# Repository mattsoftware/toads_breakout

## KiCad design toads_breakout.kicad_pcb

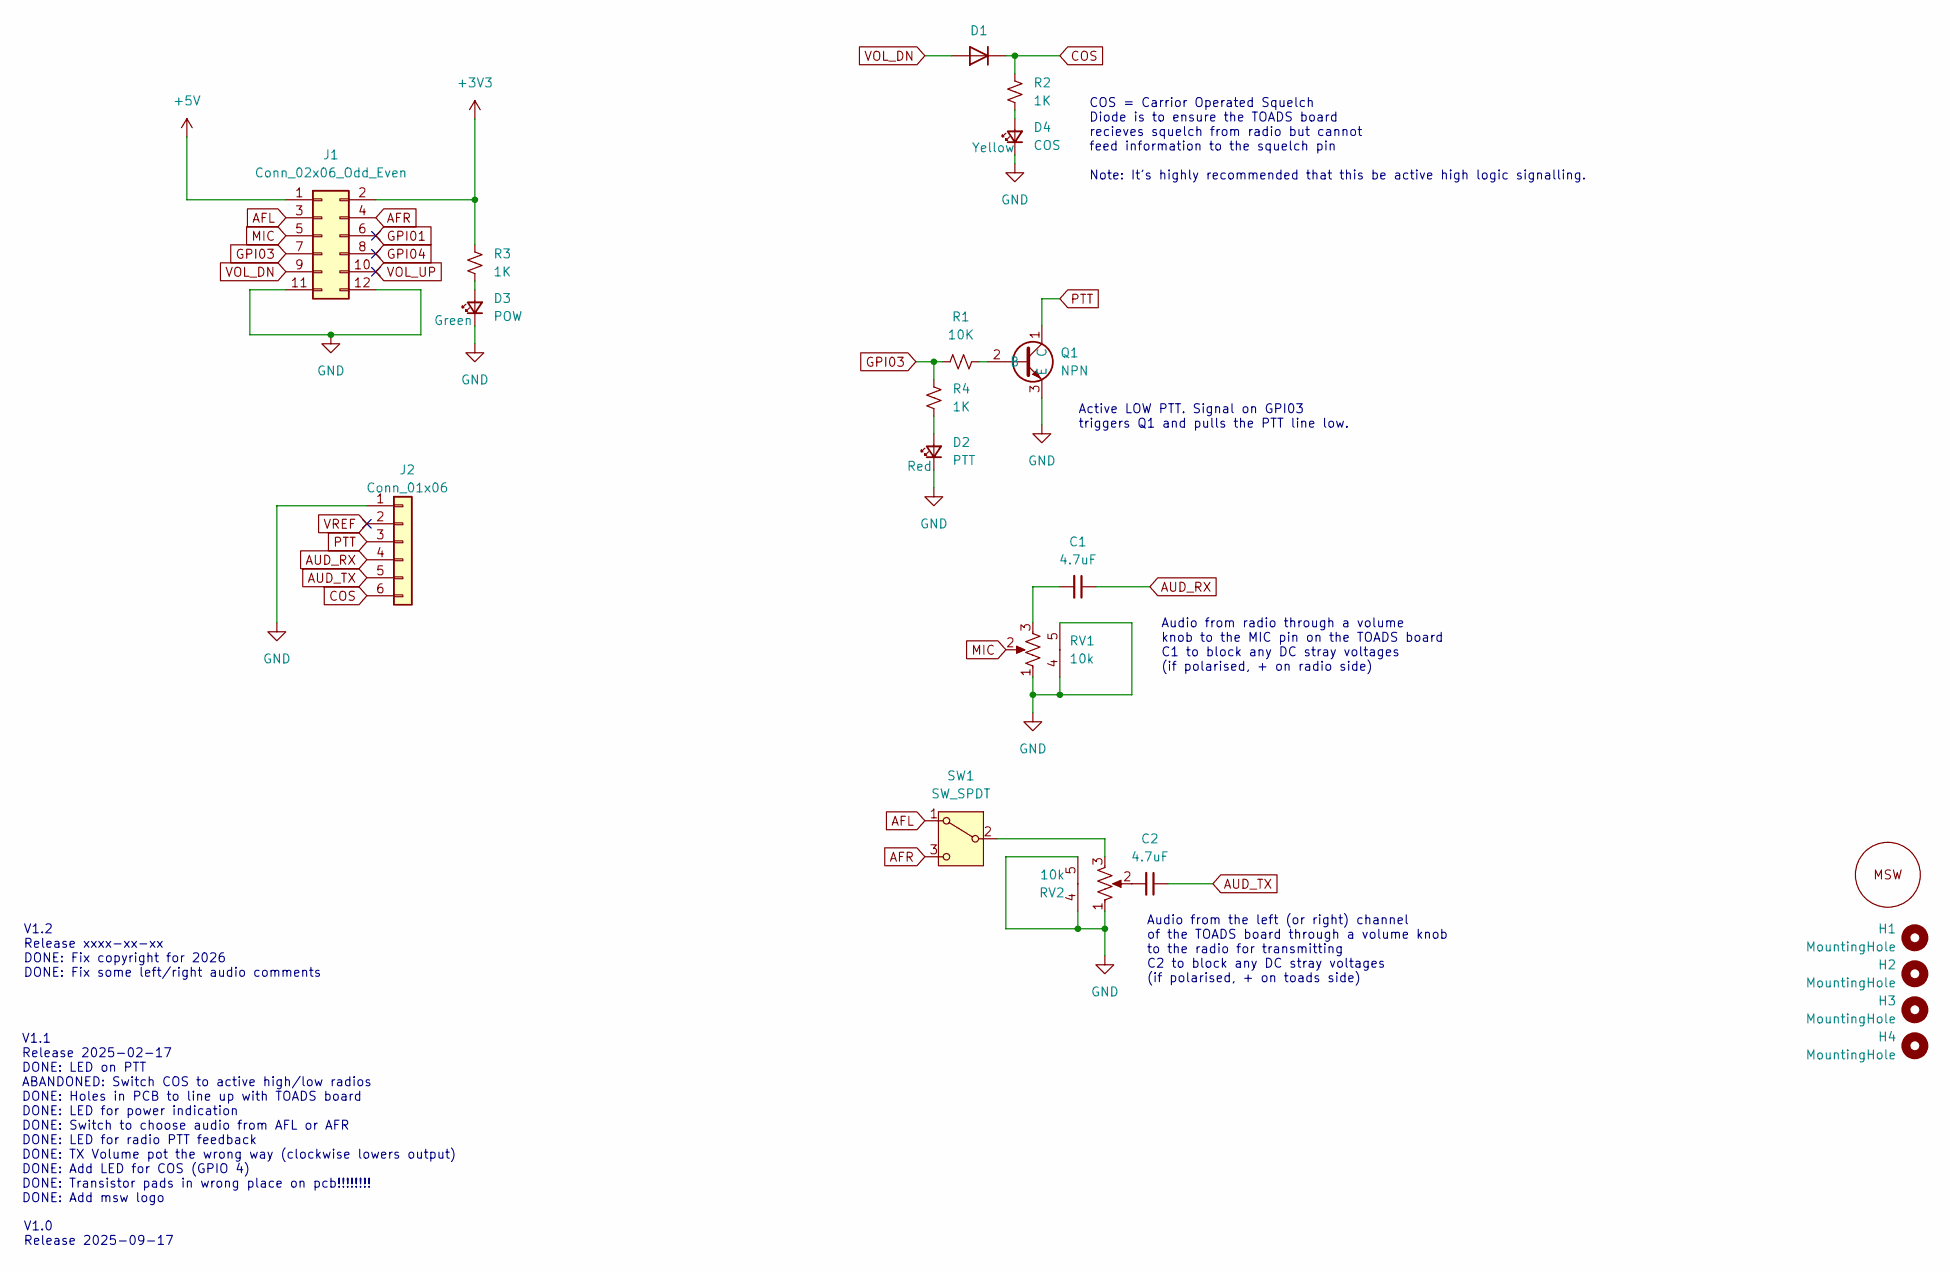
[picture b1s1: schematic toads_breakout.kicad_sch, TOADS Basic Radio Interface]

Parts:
C1, C2: 4.7uF; C_0805_2012Metric_Pad1.18x1.45mm_HandSolder; LCSC# C1779
D1: D_SOD-123FL; LCSC# C64898
D2: PTT; LED_0805_2012Metric; LCSC# C84256
D3: POW; LED_0805_2012Metric; LCSC# C2297
D4: COS; LED_0805_2012Metric; LCSC# C2296
H1, H2, H3, H4: MountingHole; MountingHole_2.5mm_Pad
J1: Conn_02x06_Odd_Even; PinHeader_2x06_P2.54mm_Vertical; LCSC# C124388
J2: Conn_01x06; PinHeader_1x06_P2.54mm_Vertical; LCSC# C37208
Q1: NPN; SOT-23_Handsoldering; LCSC# C2145
R1: 10K; R_0805_2012Metric_Pad1.20x1.40mm_HandSolder; LCSC# C17414
R2, R3, R4: 1K; R_0805_2012Metric_Pad1.20x1.40mm_HandSolder; LCSC# C17513
RV1, RV2: 10k; R_Potentiometer-10k-C361173; LCSC# C361173
SW1: SW_SPDT; SW-SPDT-C49023767; LCSC# C49023767
U1: MSW_Logo; MSW

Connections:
+3V3: J1.2, R3.1
+5V: J1.1
AFL: J1.3, SW1.1 (A)
AFR: J1.4, SW1.3 (C)
AUD_RX: C1.1, J2.4
AUD_TX: C2.1, J2.5
COS: D1.1 (K), J2.6, R2.1
GND: D2.1 (K), D3.1 (K), D4.1 (K), J1.11, J1.12, J2.1, Q1.3 (E), RV1.1, RV1.4, RV1.5, RV2.1, RV2.4, RV2.5
GPI01: J1.6
GPI03: J1.7, R1.1, R4.1
GPI04: J1.8
MIC: J1.5, RV1.2
unnamed: C1.2, RV1.3
unnamed: C2.2, RV2.2
unnamed: D2.2 (A), R4.2
unnamed: D3.2 (A), R3.2
unnamed: D4.2 (A), R2.2
unnamed: Q1.2 (B), R1.2
unnamed: RV2.3, SW1.2 (B)
PTT: J2.3, Q1.1 (C)
VOL_DN: D1.2 (A), J1.9
VOL_UP: J1.10
VREF: J2.2

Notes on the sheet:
Audio from radio through a volume knob to the MIC pin on the TOADS board C1 to block any DC stray voltages (if polarised, + on radio side)
Audio from the left (or right) channel of the TOADS board through a volume knob to the radio for transmitting C2 to block any DC stray voltages (if polarised, + on toads side)
COS = Carrior Operated Squelch Diode is to ensure the TOADS board recieves squelch from radio but cannot feed information to the squelch pin Note: It's highly recommended that this be active high logic signalling.
V1.1 Release 2025-02-17 DONE: LED on PTT ABANDONED: Switch COS to active high/low radios DONE: Holes in PCB to line up with TOADS board DONE: LED for power indication DONE: Switch to choose audio from AFL or AFR DONE: LED for radio PTT feedback DONE: TX Volume pot the wrong way (clockwise lowers ou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
V1.0 Release 2025-09-17
V1.2 Release xxxx-xx-xx DONE: Fix copyright for 2026 DONE: Fix some left/right audio comments
Active LOW PTT. Signal on GPI03 triggers Q1 and pulls the PTT line low.

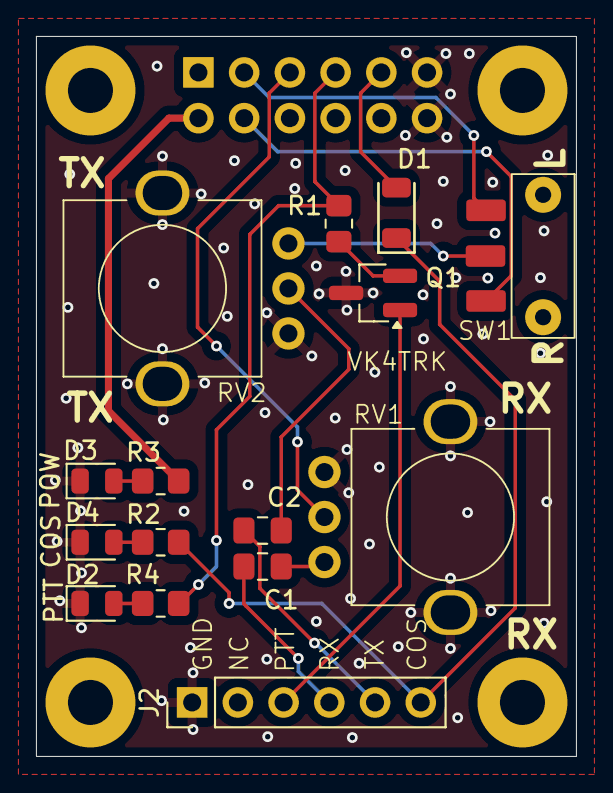
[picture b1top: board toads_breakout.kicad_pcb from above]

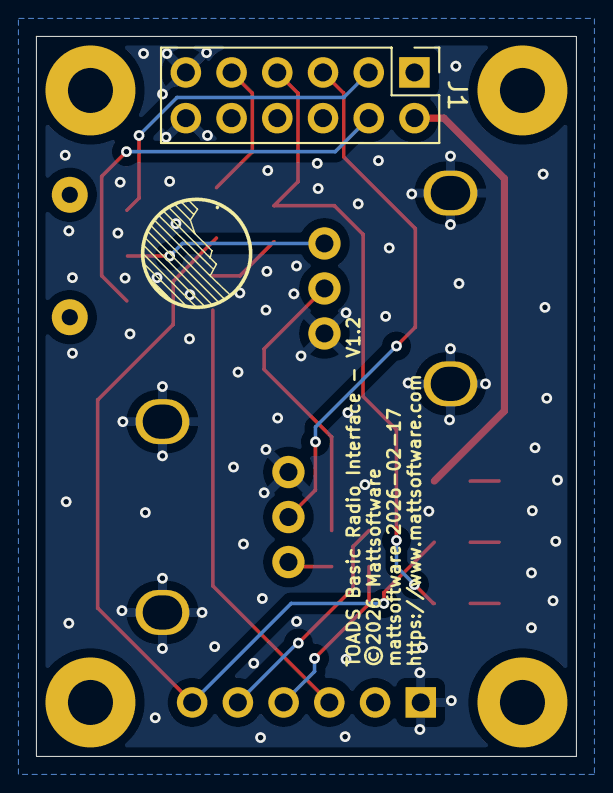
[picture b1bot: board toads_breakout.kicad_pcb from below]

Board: 2 copper layers, 30.0 x 40.0 mm, 21 parts (2 on the bottom side), 18 nets.

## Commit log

2025-09-17 V1.0
2026-02-17 v1.1
2026-02-17 Bump to v1.1 - not released yet

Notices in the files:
toads_breakout.kicad_pcb:
©2026 Mattsoftware
License: CC By 4.0
https://creativecommons.org/licenses/by/4.0
